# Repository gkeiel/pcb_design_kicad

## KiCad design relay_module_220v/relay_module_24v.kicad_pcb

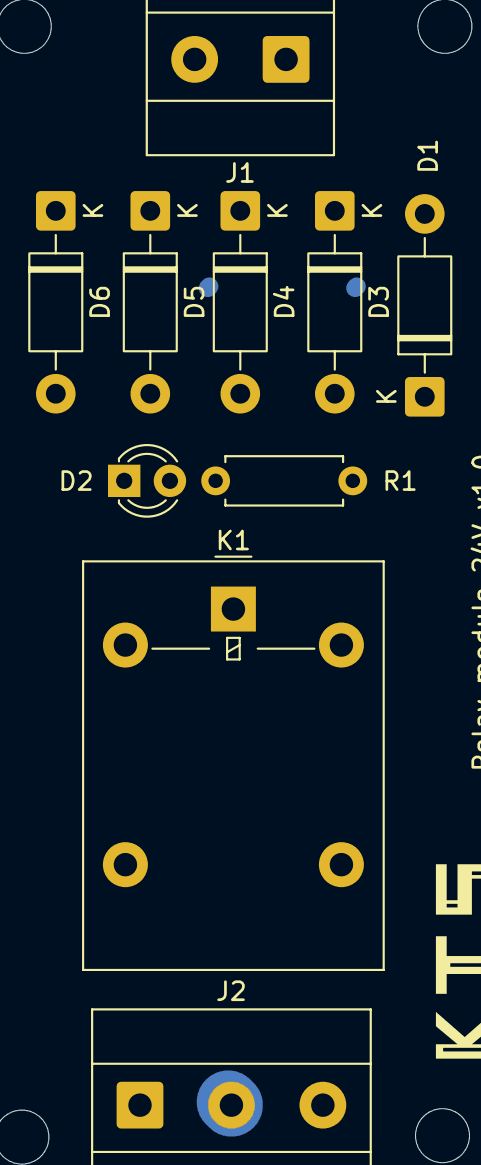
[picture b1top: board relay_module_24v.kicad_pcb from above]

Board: 2 copper layers, 10 parts (0 on the bottom side), 8 nets.

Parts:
D1, D3, D4, D5, D6: 1N4007; D_DO-41_SOD81_P10.16mm_Horizontal
D2: LED; LED_D3.0mm
J1: Conn_01x02_Pin; TerminalBlock_Phoenix_MKDS-1,5-2-5.08_1x02_P5.08mm_Horizont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
J2: Conn_01x03_Pin; TerminalBlock_Phoenix_MKDS-1,5-3-5.08_1x03_P5.08mm_Horizont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
K1: Relay_SPDT; Relay_SPDT_Omron-G5LE-1
R1: R; R_Axial_DIN0207_L6.3mm_D2.5mm_P7.62mm_Horizontal

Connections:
C_1: J2.2, K1.3
GND: D1.2 (A), D2.1 (K), D4.2 (A), D6.2 (A), K1.2
NC_1: J2.3, K1.4
NO_1: J2.1, K1.5
unnamed: D1.1 (K), D3.1 (K), D5.1 (K), K1.1, R1.1
unnamed: D2.2 (A), R1.2
unnamed: D3.2 (A), D4.1 (K), J1.1
unnamed: D5.2 (A), D6.1 (K), J1.2
